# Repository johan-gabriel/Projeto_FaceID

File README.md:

## Projeto_FaceID
Código fonte para controle da RP2040 em C

## Resumo
Firmware desenvolvido a partir da data: 05/08/2022 Sistema desenvolvido para controle da Raspberry Pi Pico, que possui o microcontrolador RP2040. O código fonte foi desenvolvido em linguagem C com auxílio da SDK da Raspberry Pi Pico, utilizando a ferramenta CMake.

O circuito é responsável por bloquear o giro da catraca ou torniquete, quando não há evento de acesso pelo FaceID. Se há um evento de acesso o FaceID, que é um sistema independente, acessa o banco de dados e verifica se este acesso é autorizado para passar. Havendo a confirmação e ela sendo satisfatória, o FaceID manda um pulso seco para o circuito de controle, liberando o giro para passagem. Se for feita a tentativa de girar após o acesso, sem liberar novamente, o sistema bloqueia o próximo giro.

## IMPORTANTE
O Firmware está sujeito a mudanças devido a testes em campo. Não é o código final. 
Firmwares que possuem E têm apenas conexão com rede, mas não estão completamente implementados. 
Firmwares que possuem QR têm implementação de QRcode, mas apenas um leitor. Aguardando segunda fase com 2 leitores.

## CONFIGURAÇÕES
Para configurar o tempo de liberação pelo secBox, entre nas configurações do FaceID e coloque o tempo que deseja que fique liberado. Após isso, acione o secBox e coloque o tempo de 1500 ms para que o acionamento não altere o tempo configurado.

Na configuração do FaceID no módulo FACE NV, enquanto o sistema está online é necessário configurar como C (catraca) para que não haja conflito no acionamento do secBox e o comando vindo do Catraca. Quando sem rede o sistema irá continuar funcionando, pois quando o FaceID perde comunicação com o módulo FACE NV, o mesmo aciona o secBox.

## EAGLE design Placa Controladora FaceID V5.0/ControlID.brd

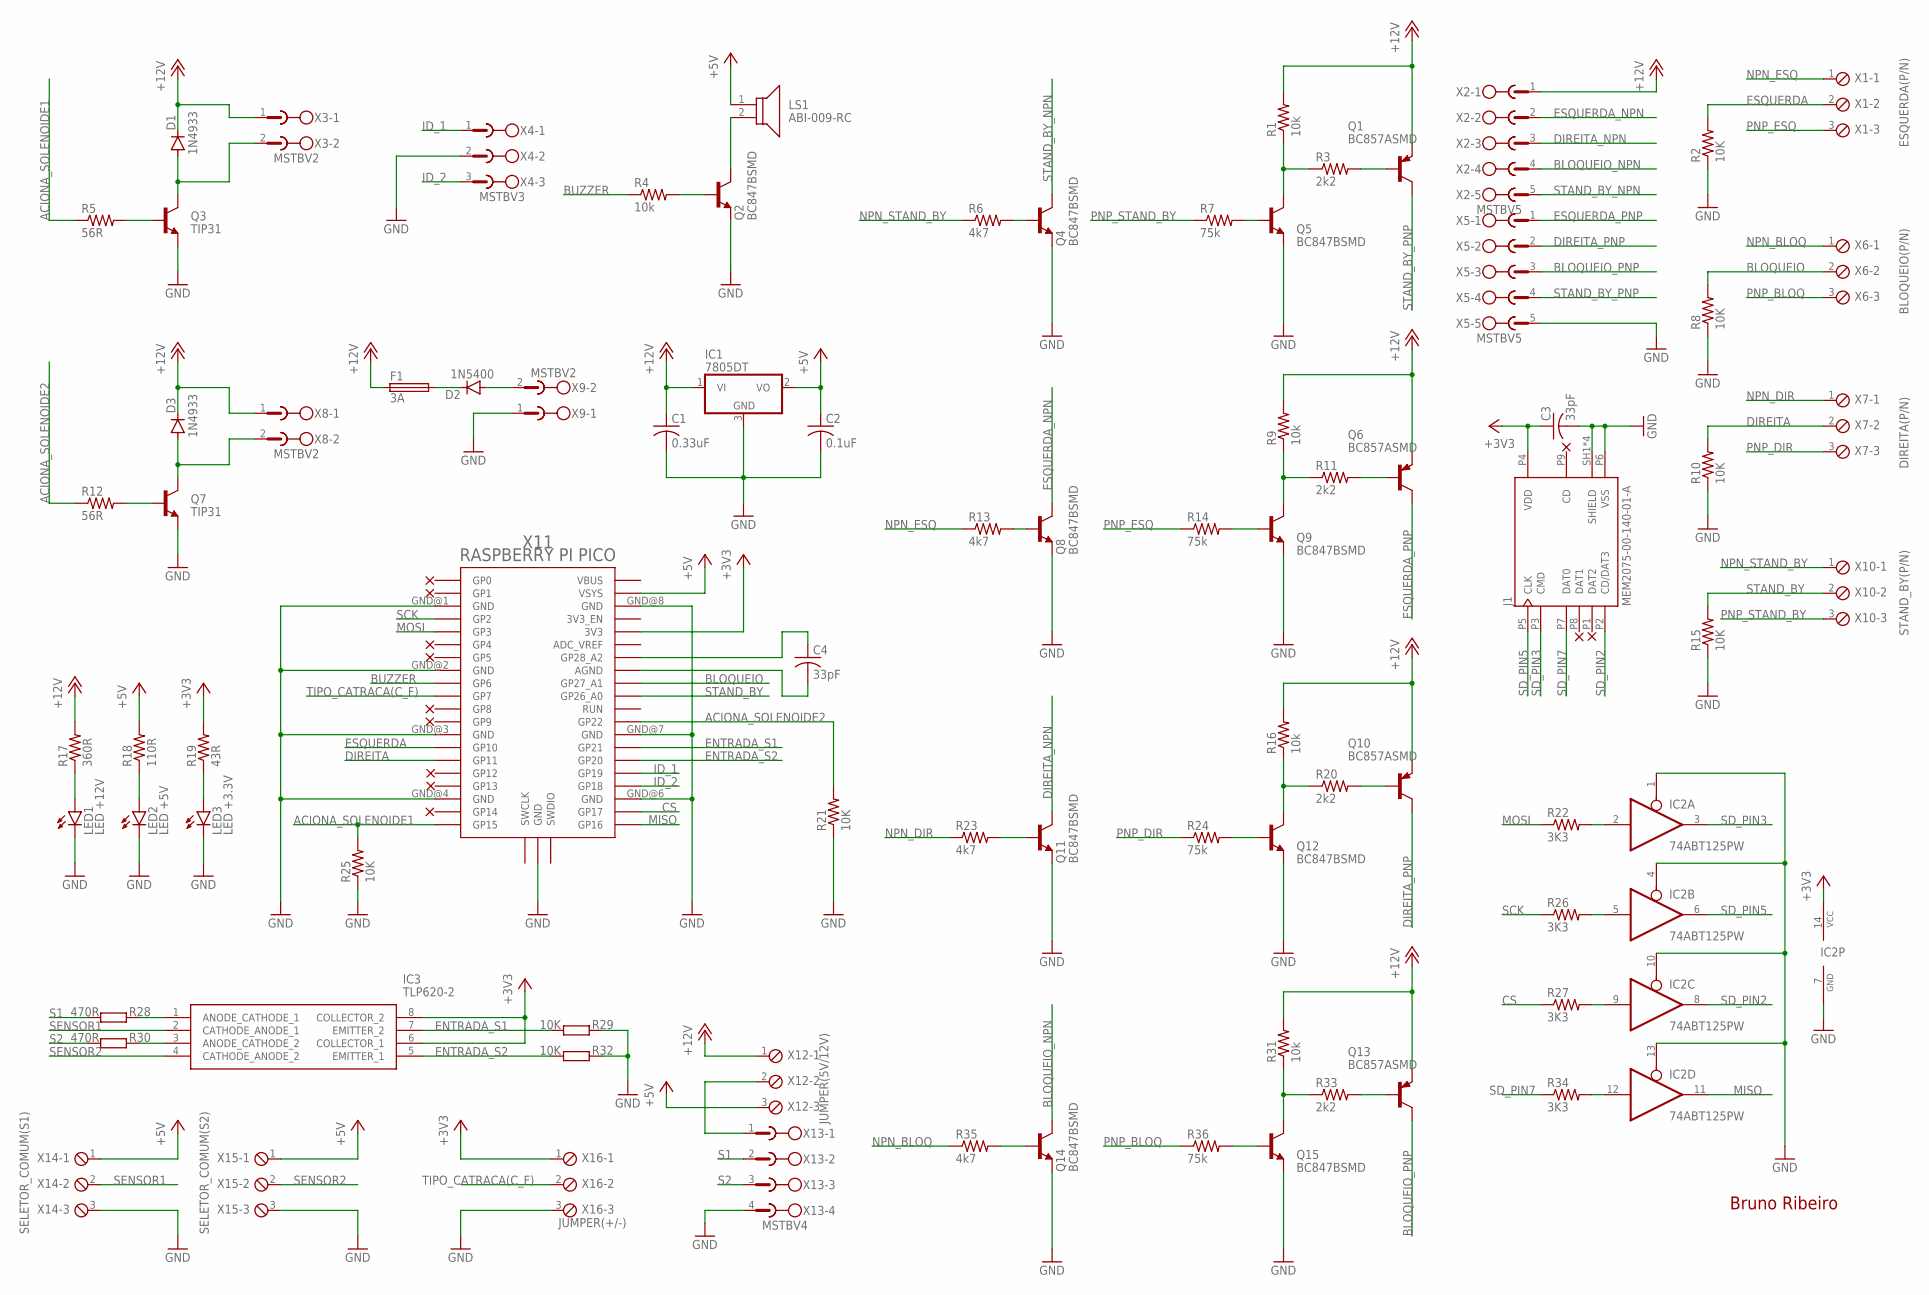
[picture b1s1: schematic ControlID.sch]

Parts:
C1: 0.33uF; C0805
C2: 0.1uF; C0805
C3, C4: 33pF; C0805
D1, D3: 1N4933; DO41-10
D2: 1N5400; DO201-15
F1: 3A; SH22,5A
IC1: 7805DT; TO252
IC2: 74ABT125PW; TSSOP14
IC3: TLP620-2; DIP762W60P254L966H485Q8N
J1: MEM2075-00-140-01-A; GCT_MEM2075-00-140-01-A
LED1: LED +12V; CHIP-LED0805
LED2: LED +5V; CHIP-LED0805
LED3: LED +3.3V; CHIP-LED0805
LS1: ABI-009-RC
Q1, Q6, Q10, Q13: BC857ASMD; SOT23-BEC
Q2, Q4, Q5, Q8, Q9, Q11, Q12, Q14, Q15: BC847BSMD; SOT23
Q3, Q7: TIP31; TO254P1060X482X2222-3
R1, R4, R9, R16, R31: 10k; R0805
R2, R8, R10, R15, R21, R25, R29, R32: 10K; R0805
R3, R11, R20, R33: 2k2; R0805
R5, R12: 56R; R0805
R6, R13, R23, R35: 4k7; R0805
R7, R14, R24, R36: 75k; R0805
R17: 360R; R0805
R18: 110R; R0805
R19: 43R; R0805
R22, R26, R27, R34: 3K3; R0805
R28, R30: 470R; R0805
X1: ESQUERDA(P/N); 3POL254
X2, X5: MSTBV5
X3, X8, X9: MSTBV2
X4: MSTBV3
X6: BLOQUEIO(P/N); 3POL254
X7: DIREITA(P/N); 3POL254
X10: STAND_BY(P/N); 3POL254
X11: RASPBERRY PI PICO; RPI_PICO_TH
X12: JUMPER(5V/12V); 3POL254
X13: MSTBV4
X14: SELETOR_COMUM(S1); 3POL254
X15: SELETOR_COMUM(S2); 3POL254
X16: JUMPER(+/-); 3POL254

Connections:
+3V3: C3.1, IC2.14 (VCC), IC3.6 (COLLECTOR_1), IC3.8 (COLLECTOR_2), J1.P4 (VDD), R19.2, X11.3V3, X16.1
+5V: C2.1, IC1.2 (VO), LS1.1, R18.2, X11.VSYS, X12.3, X14.1, X15.1
+12V: C1.1, D1.C, D3.C, F1.1, IC1.1 (VI), Q1.E, Q6.E, Q10.E, Q13.E, R1.2, R9.2, R16.2, R17.2, R31.2, X2.1, X3.1, X8.1, X12.1
ACIONA_SOLENOIDE1: R5.1, R25.2, X11.GP15
ACIONA_SOLENOIDE2: R12.1, R21.2, X11.GP22
BLOQUEIO: R8.2, X6.2, X11.GP27_A1
BLOQUEIO_NPN: Q14.3 (C), X2.4
BLOQUEIO_PNP: Q13.C, X5.3
BUZZER: R4.1, X11.GP6
CS: R27.1, X11.GP17
DIREITA: R10.2, X7.2, X11.GP11
DIREITA_NPN: Q11.3 (C), X2.3
DIREITA_PNP: Q10.C, X5.2
ENTRADA_S1: IC3.7 (EMITTER_2), R29.2, X11.GP21
ENTRADA_S2: IC3.5 (EMITTER_1), R32.2, X11.GP20
ESQUERDA: R2.2, X1.2, X11.GP10
ESQUERDA_NPN: Q8.3 (C), X2.2
ESQUERDA_PNP: Q6.C, X5.1
GND: C1.2, C2.2, C3.2, IC1.3 (GND), IC2.1 (OE), IC2.4 (OE), IC2.7 (GND), IC2.10 (OE), IC2.13 (OE), J1.P6 (VSS), J1.SH1 (SHIELD), J1.SH2 (SHIELD), J1.SH3 (SHIELD), J1.SH4 (SHIELD), LED1.C, LED2.C, LED3.C, Q2.2 (E), Q3.3 (E), Q4.2 (E), Q5.2 (E), Q7.3 (E), Q8.2 (E), Q9.2 (E), Q11.2 (E), Q12.2 (E), Q14.2 (E), Q15.2 (E), R2.1, R8.1, R10.1, R15.1, R21.1, R25.1, R29.1, R32.1, X4.2, X5.5, X9.1, X11.GND@1 (GND), X11.GND@2 (GND), X11.GND@3 (GND), X11.GND@4 (GND), X11.GND@5 (GND), X11.GND@6 (GND), X11.GND@7 (GND), X11.GND@8 (GND), X13.4, X14.3, X15.3, X16.3
ID_1: X4.1, X11.GP19
ID_2: X4.3, X11.GP18
MISO: IC2.11 (O), X11.GP16
MOSI: R22.1, X11.GP3
unnamed: Q3.1 (B), R5.2
unnamed: Q7.1 (B), R12.2
unnamed: X12.2, X13.1
unnamed: D2.A, X9.2
unnamed: Q8.1 (B), R13.2
unnamed: LED1.A, R17.1
unnamed: LED2.A, R18.1
unnamed: LED3.A, R19.1
unnamed: D2.C, F1.2
unnamed: Q4.1 (B), R6.2
unnamed: D1.A, Q3.2 (C), X3.2
unnamed: Q9.3 (C), R9.1, R11.1
unnamed: D3.A, Q7.2 (C), X8.2
unnamed: Q9.1 (B), R14.2
unnamed: Q6.B, R11.2
unnamed: Q15.3 (C), R31.1, R33.1
unnamed: Q5.3 (C), R1.1, R3.1
unnamed: Q5.1 (B), R7.2
unnamed: Q11.1 (B), R23.2
unnamed: Q1.B, R3.2
unnamed: Q15.1 (B), R36.2
unnamed: Q14.1 (B), R35.2
unnamed: C4.1, X11.GP28_A2
unnamed: Q13.B, R33.2
unnamed: C4.2, X11.AGND
unnamed: Q12.3 (C), R16.1, R20.1
unnamed: Q2.1 (B), R4.2
unnamed: Q12.1 (B), R24.2
unnamed: Q10.B, R20.2
unnamed: LS1.2, Q2.3 (C)
unnamed: IC3.3 (ANODE_CATHODE_2), R30.1
unnamed: IC3.1 (ANODE_CATHODE_1), R28.1
unnamed: IC2.2 (I), R22.2
unnamed: IC2.5 (I), R26.2
unnamed: IC2.9 (I), R27.2
unnamed: IC2.12 (I), R34.2
NPN_BLOQ: R35.1, X6.1
NPN_DIR: R23.1, X7.1
NPN_ESQ: R13.1, X1.1
NPN_STAND_BY: R6.1, X10.1
PNP_BLOQ: R36.1, X6.3
PNP_DIR: R24.1, X7.3
PNP_ESQ: R14.1, X1.3
PNP_STAND_BY: R7.1, X10.3
S1: R28.2, X13.2
S2: R30.2, X13.3
SCK: R26.1, X11.GP2
SD_PIN2: IC2.8 (O), J1.P2 (CD/DAT3)
SD_PIN3: IC2.3 (O), J1.P3 (CMD)
SD_PIN5: IC2.6 (O), J1.P5 (CLK)
SD_PIN7: J1.P7 (DAT0), R34.1
SENSOR1: IC3.2 (CATHODE_ANODE_1), X14.2
SENSOR2: IC3.4 (CATHODE_ANODE_2), X15.2
STAND_BY: R15.2, X10.2, X11.GP26_A0
STAND_BY_NPN: Q4.3 (C), X2.5
STAND_BY_PNP: Q1.C, X5.4
TIPO_CATRACA(C_F): X11.GP7, X16.2

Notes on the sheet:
Bruno Ribeiro

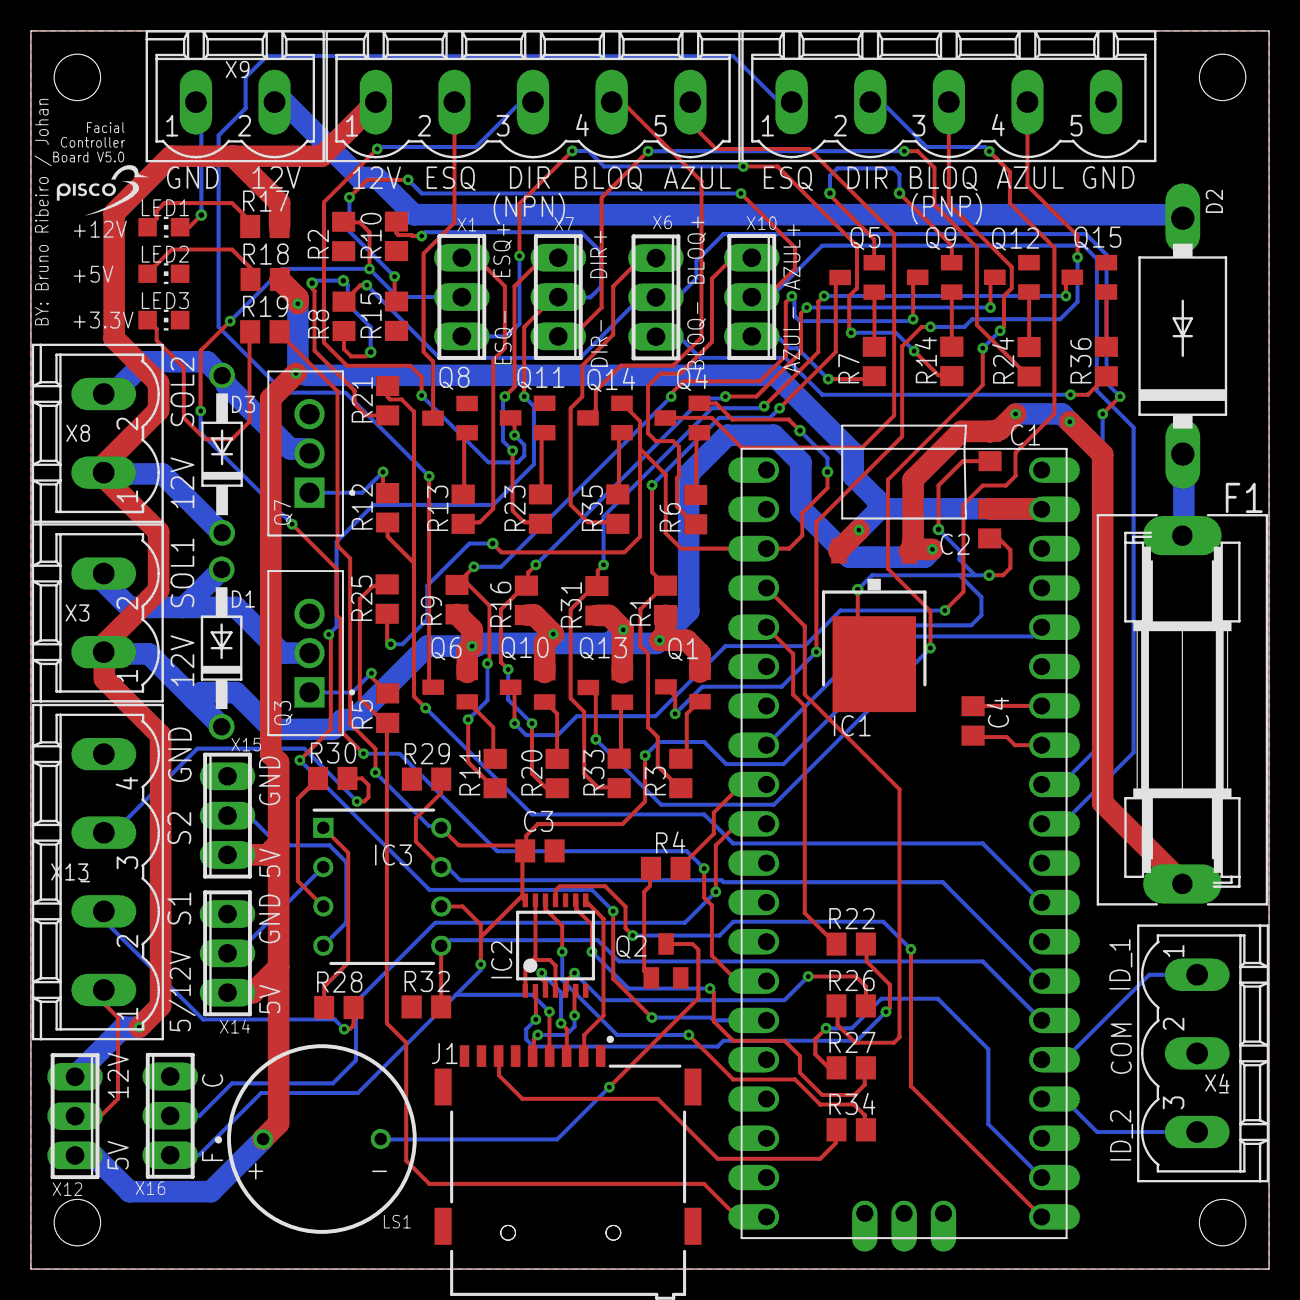
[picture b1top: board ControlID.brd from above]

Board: 2 copper layers, 80.0 x 80.0 mm, 83 parts (0 on the bottom side), 80 nets.

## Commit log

2022-09-20 Versão 1.0 do Controle de catracas com e sem SSLon
2022-09-20 Videos e Imagens do Projeto
2022-09-22 Aviso: Só funciona em catracas Kabba, Mais informações no IMPORTANTE.TXT
2022-09-22 SSLon com catraca que possui 2 Solenóides
2022-09-26 Liberação sem o tempo atrelado ao FaceID
2022-09-26 Liberação com regulagem de tempo atrelado ao FaceID
2022-09-26 Configuração de tempo remoto
2022-10-07 Bild da V2 feita
2023-07-18 Atualizações de sistema
2023-11-08 Atualização Ethernet
2023-11-24 Atualização modulo SD_SPI_FATFS
2023-11-28 Aquivos PCB
2023-12-12 Integração Qrcode unico
2024-01-18 25EQR1 e 2
2024-01-23 ComTratamentoDeComando
2024-01-23 CorreçãoSLLon
2024-01-26 Ajustes_na_liberação
2024-01-31 Firmware BackupFinal
2024-01-31 Firmware Final
2024-01-31 Lib no-OS-FatFS
2024-01-31 Add SSH para SSL
2024-02-07 Erros: RPAn e Sol SSLon
2024-03-19 Picto,SPG
2024-04-05 SNE,qrcode
2024-08-08 Novas att Ribas
2024-08-27 Correcao Giro forçado
2024-08-27 Firmware43
2025-04-17 Adição das novas versões e correções
